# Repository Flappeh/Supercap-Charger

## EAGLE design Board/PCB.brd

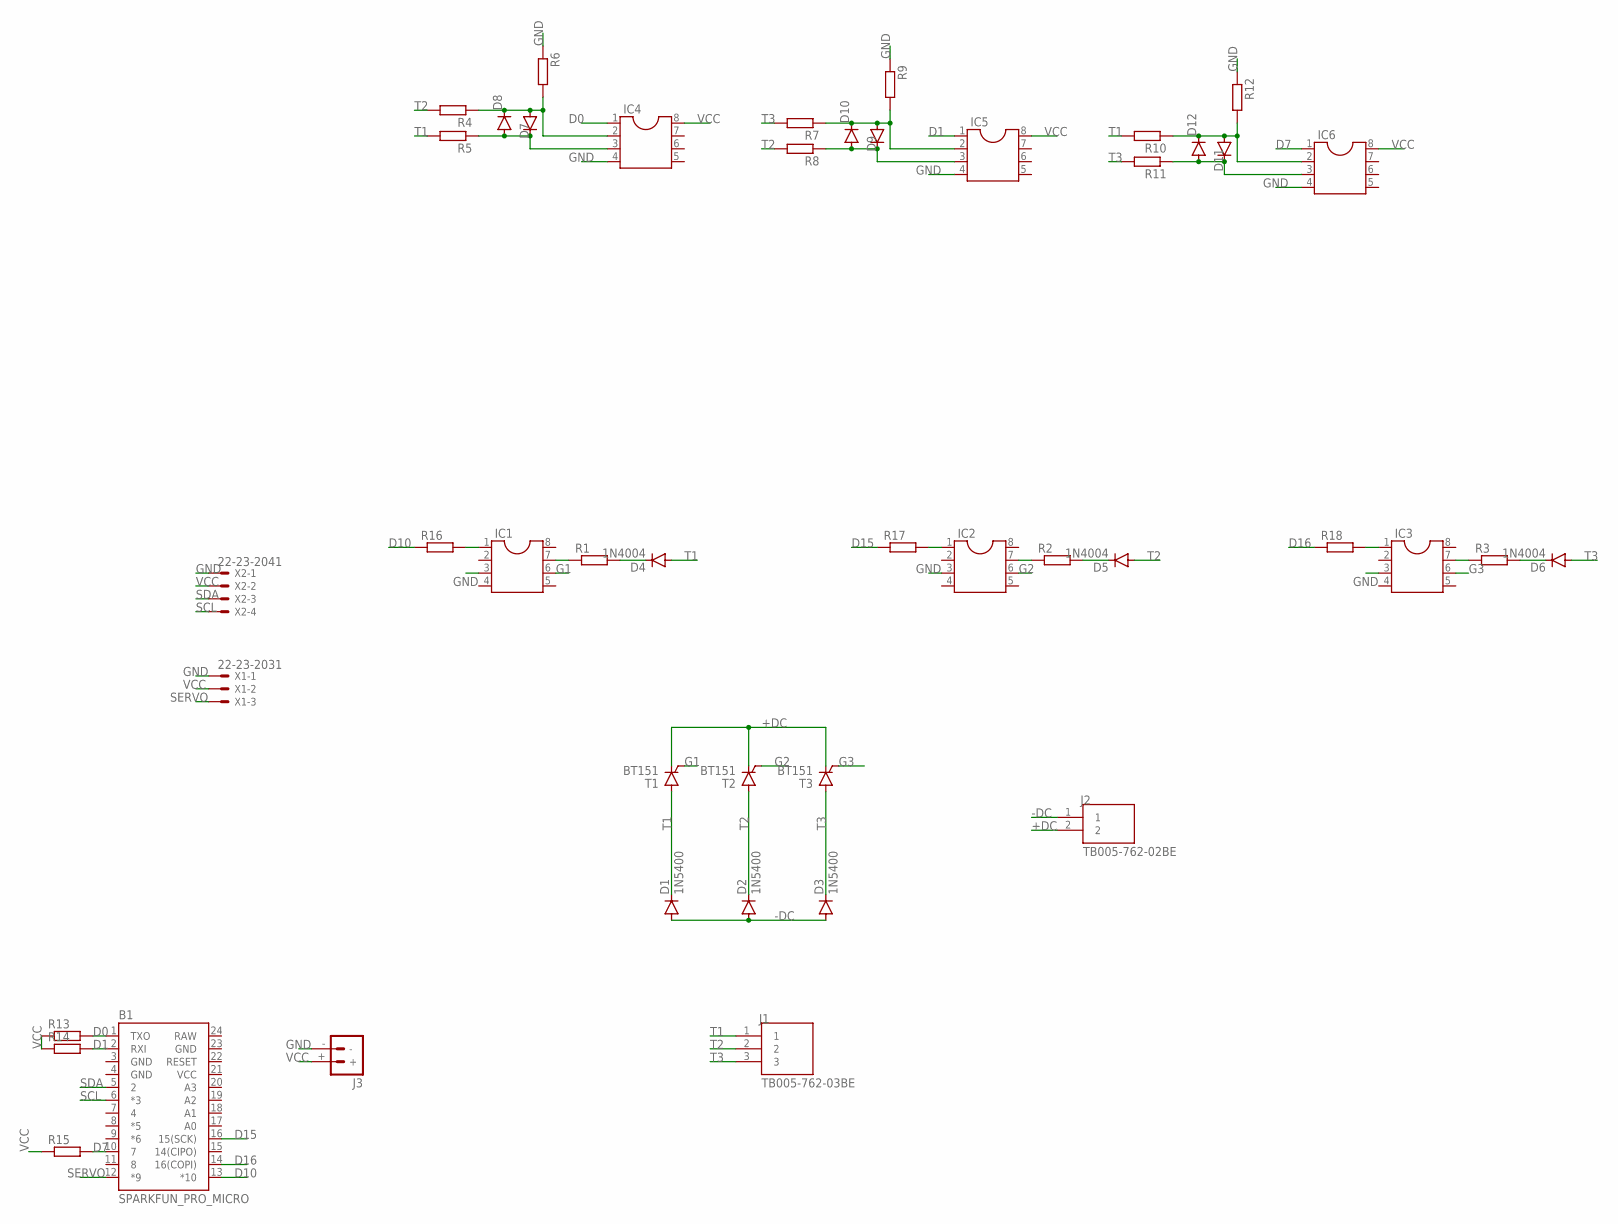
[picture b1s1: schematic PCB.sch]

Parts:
B1: SPARKFUN_PRO_MICRO
D1, D2, D3: 1N5400; DO201-15
D4, D5, D6, D7, D8, D9, D10, D11, D12: 1N4004; DO41-10
IC1, IC2, IC3, IC4, IC5, IC6: DIL8; DIL08
J1: TB005-762-03BE; CUI_TB005-762-03BE
J2: TB005-762-02BE; CUI_TB005-762-02BE
J3: BATTERY_CONN_DEANS; DEANS
R1, R2, R3, R4, R5, R6, R7, R8, R9, R10, R11, R12, R13, R14, R15, R16, R17, R18: R-EU_0207/10; 0207/10
T1, T2, T3: BT151; TO220CL
X1: 22-23-2031
X2: 22-23-2041

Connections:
+DC: J2.2, T1.C, T2.C, T3.C
-DC: D1.A, D2.A, D3.A, J2.1
D0: B1.1 (TXO), IC4.1, R13.2
D1: B1.2 (RXI), IC5.1, R14.2
D7: B1.10 (7), IC6.1, R15.2
D10: B1.13 (*10), R16.1
D15: B1.16 (15(SCK)), R17.1
D16: B1.14 (16(COPI)), R18.1
G1: IC1.6, T1.G
G2: IC2.6, T2.G
G3: IC3.6, T3.G
GND: B1.3 (GND), B1.4 (GND), B1.23 (GND), IC1.3, IC2.3, IC3.3, IC4.4, IC5.4, IC6.4, J3.-, R6.1, R9.1, R12.1, X1.1, X2.1
unnamed: IC1.1, R16.2
unnamed: IC2.1, R17.2
unnamed: D7.C, D8.A, IC4.3, R5.1
unnamed: D7.A, D8.C, IC4.2, R4.1, R6.2
unnamed: IC3.1, R18.2
unnamed: IC1.7, R1.1
unnamed: D4.C, R1.2
unnamed: IC2.7, R2.1
unnamed: D5.C, R2.2
unnamed: IC3.7, R3.1
unnamed: D6.C, R3.2
unnamed: D9.C, D10.A, IC5.3, R8.1
unnamed: D9.A, D10.C, IC5.2, R7.1, R9.2
unnamed: D11.C, D12.A, IC6.3, R11.1
unnamed: D11.A, D12.C, IC6.2, R10.1, R12.2
RAW: B1.24 (RAW)
SCL: B1.6 (*3), X2.4
SDA: B1.5 (2), X2.3
SERVO: B1.12 (*9), X1.3
T1: D1.C, D4.A, J1.1, R5.2, R10.2, T1.A
T2: D2.C, D5.A, J1.2, R4.2, R8.2, T2.A
T3: D3.C, D6.A, J1.3, R7.2, R11.2, T3.A
VCC: B1.21 (VCC), IC4.8, IC5.8, IC6.8, J3.+, R13.1, R14.1, R15.1, X1.2, X2.2

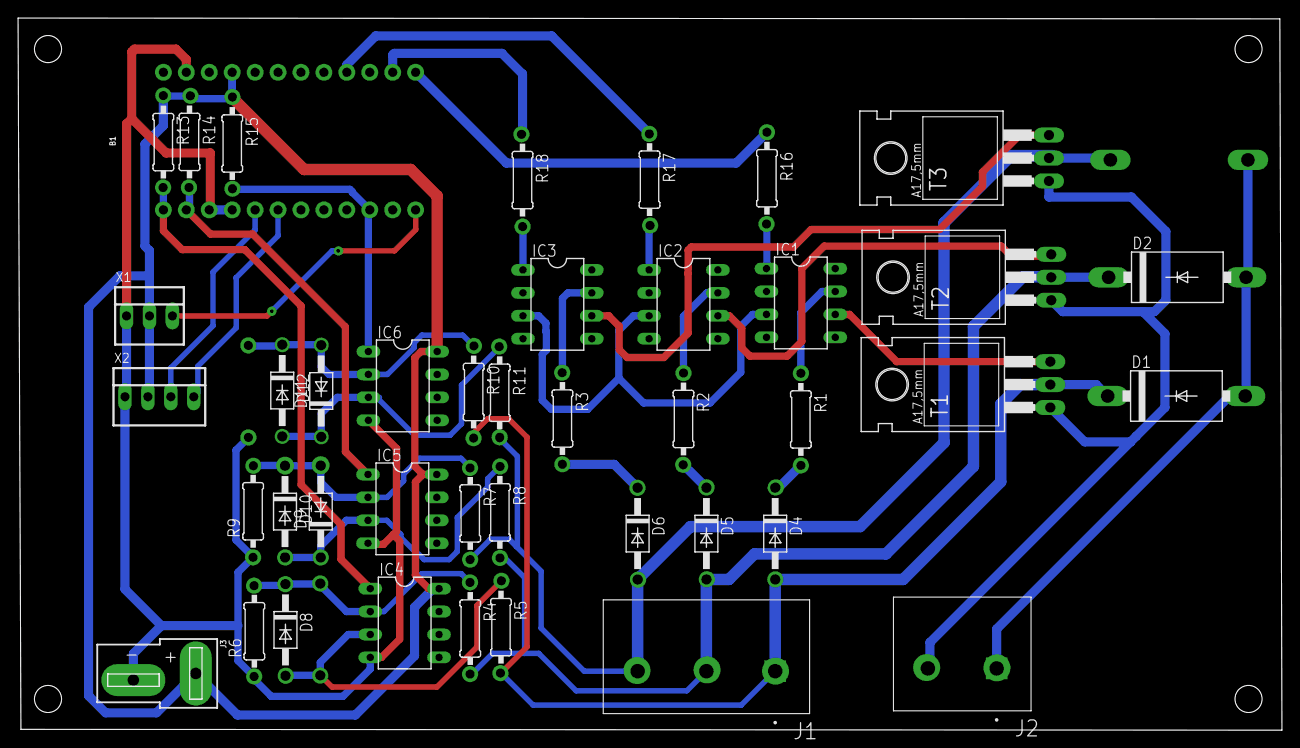
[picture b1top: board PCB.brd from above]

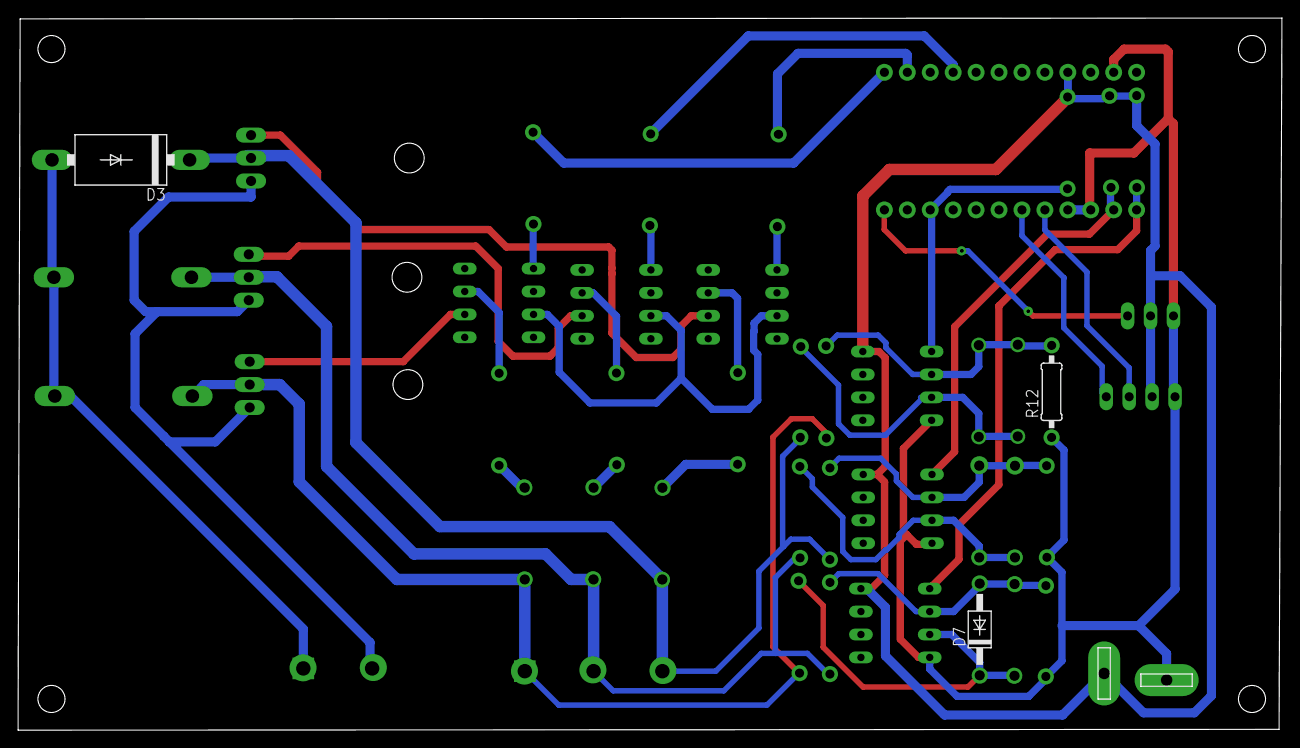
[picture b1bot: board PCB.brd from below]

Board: 2 copper layers, 139.9 x 78.8 mm, 45 parts (3 on the bottom side), 34 nets.

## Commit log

2022-08-19 add boards, code, and PCBSchematics

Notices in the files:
parts and their libraries:
SparkFun-Boards: Licensing: Creative Commons ShareAlike 4.0 International - https://creativecommons.org/licenses/by-sa/4.0
